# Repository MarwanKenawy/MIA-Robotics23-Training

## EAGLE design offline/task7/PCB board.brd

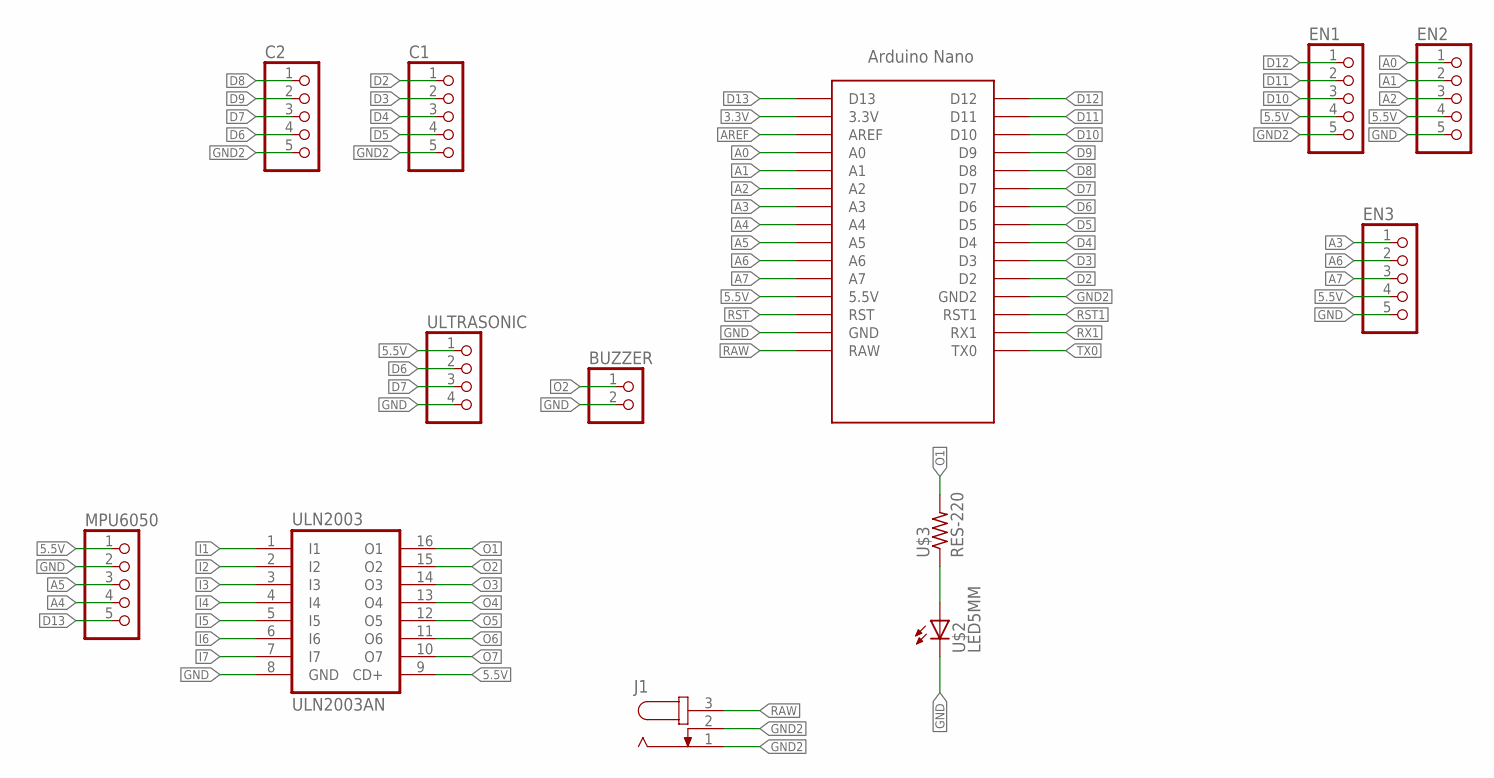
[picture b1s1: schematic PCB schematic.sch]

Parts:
BUZZER: PINHD-1X2; 1X02
C1, C2: PINHD-1X5; 1X05
EN1, EN2, EN3: PINHD-1X5; 1X05
J1: JACK-PLUG0; SPC4077
MPU6050: PINHD-1X5; 1X05
U$1: ARDUINO_NANO; NANO
U$2: LED5MM
U$3: RES-220; 0204/5
ULN2003: ULN2003AN; DIL16
ULTRASONIC: PINHD-1X4; 1X04

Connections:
3.3V: U$1.3.3V
5.5V: EN1.4, EN2.4, EN3.4, MPU6050.1, U$1.5V (5.5V), ULN2003.9 (CD+), ULTRASONIC.1
A0: EN2.1, U$1.A0
A1: EN2.2, U$1.A1
A2: EN2.3, U$1.A2
A3: EN3.1, U$1.A3
A4: MPU6050.4, U$1.A4
A5: MPU6050.3, U$1.A5
A6: EN3.2, U$1.A6
A7: EN3.3, U$1.A7
AREF: U$1.AREF
D2: C1.1, U$1.D2
D3: C1.2, U$1.D3
D4: C1.3, U$1.D4
D5: C1.4, U$1.D5
D6: C2.4, U$1.D6, ULTRASONIC.2
D7: C2.3, U$1.D7, ULTRASONIC.3
D8: C2.1, U$1.D8
D9: C2.2, U$1.D9
D10: EN1.3, U$1.D10
D11: EN1.2, U$1.D11
D12: EN1.1, U$1.D12
D13: MPU6050.5, U$1.D13
GND: BUZZER.2, EN2.5, EN3.5, MPU6050.2, U$1.GND, U$2.K (C), ULN2003.8 (GND), ULTRASONIC.4
GND2: C1.5, C2.5, EN1.5, J1.1, J1.2, U$1.GND1 (GND2)
I1: ULN2003.1 (I1)
I2: ULN2003.2 (I2)
I3: ULN2003.3 (I3)
I4: ULN2003.4 (I4)
I5: ULN2003.5 (I5)
I6: ULN2003.6 (I6)
I7: ULN2003.7 (I7)
unnamed: U$2.A, U$3.1
O1: U$3.2, ULN2003.16 (O1)
O2: BUZZER.1, ULN2003.15 (O2)
O3: ULN2003.14 (O3)
O4: ULN2003.13 (O4)
O5: ULN2003.12 (O5)
O6: ULN2003.11 (O6)
O7: ULN2003.10 (O7)
RAW: J1.3, U$1.RAW
RST: U$1.RST
RST1: U$1.RST1
RX1: U$1.RX1
TX0: U$1.TX0

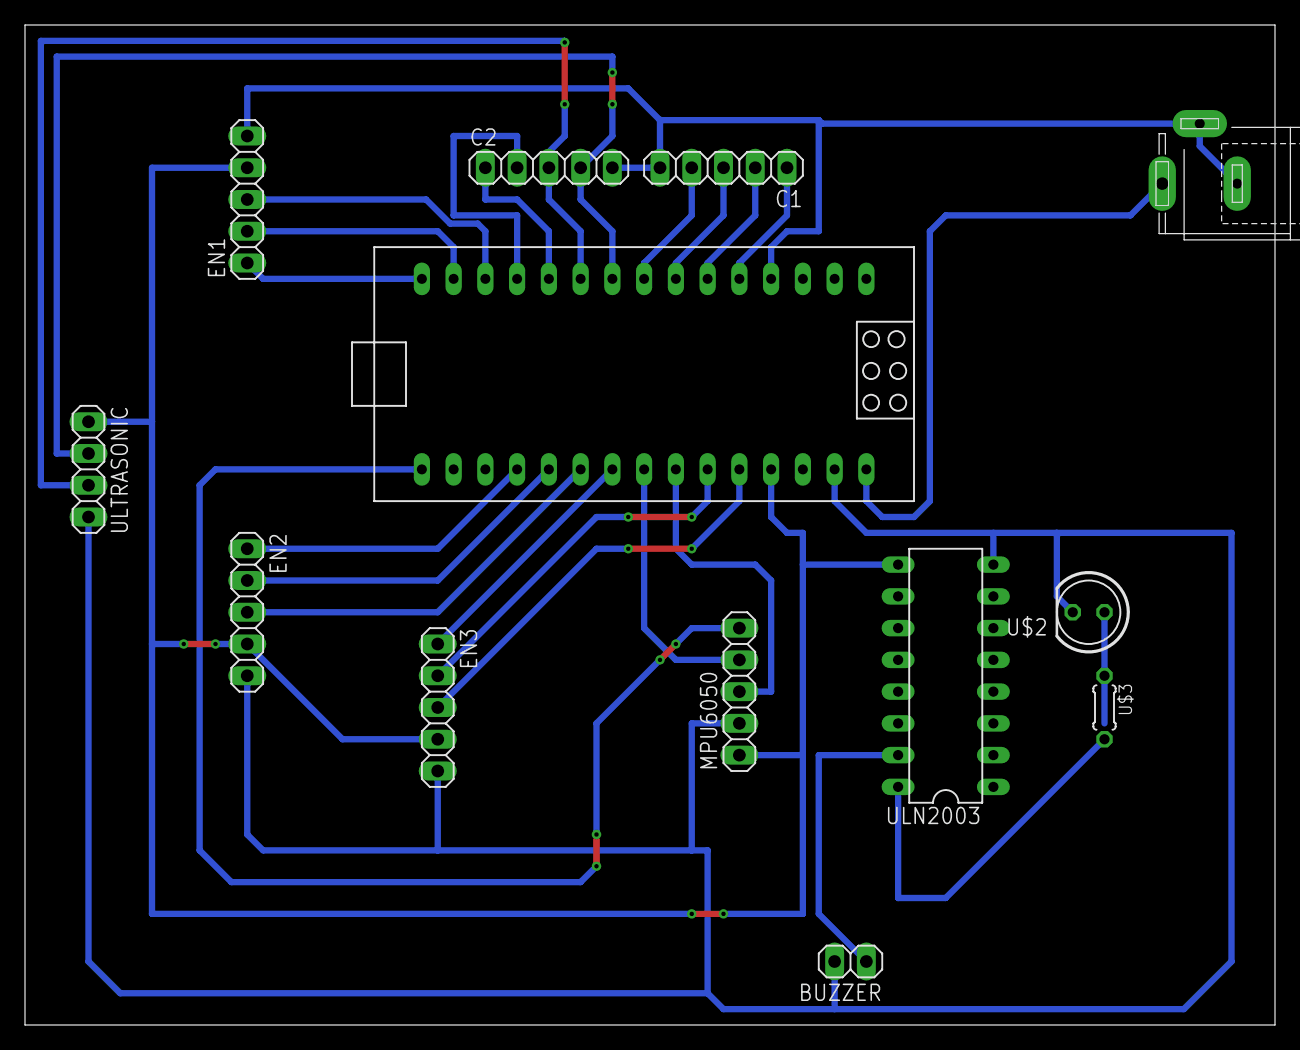
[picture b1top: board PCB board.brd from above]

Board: 2 copper layers, 100.0 x 80.0 mm, 13 parts (0 on the bottom side), 27 nets.

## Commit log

2022-08-09 online/task1
2022-08-09 online/task2
2022-08-09 online/task3
2022-08-09 online/task4
2022-08-15 offline/task2
2022-08-15 offline/task3
2022-08-15 online/taskx
2022-08-15 Revert "online/taskx"
    This reverts commit e23f9dd0e981f95a99a3a7072c46b65b6316ca37.
2022-08-15 Revert "Update main.py"
    This reverts commit 2c5fac9542ec015ec783adf46458494862674eaf.
2022-08-16 offline/task1
2022-08-29 offline/task4
2022-08-31 offline/task5
2022-09-04 offline/task6
2022-09-06 offline/task7
